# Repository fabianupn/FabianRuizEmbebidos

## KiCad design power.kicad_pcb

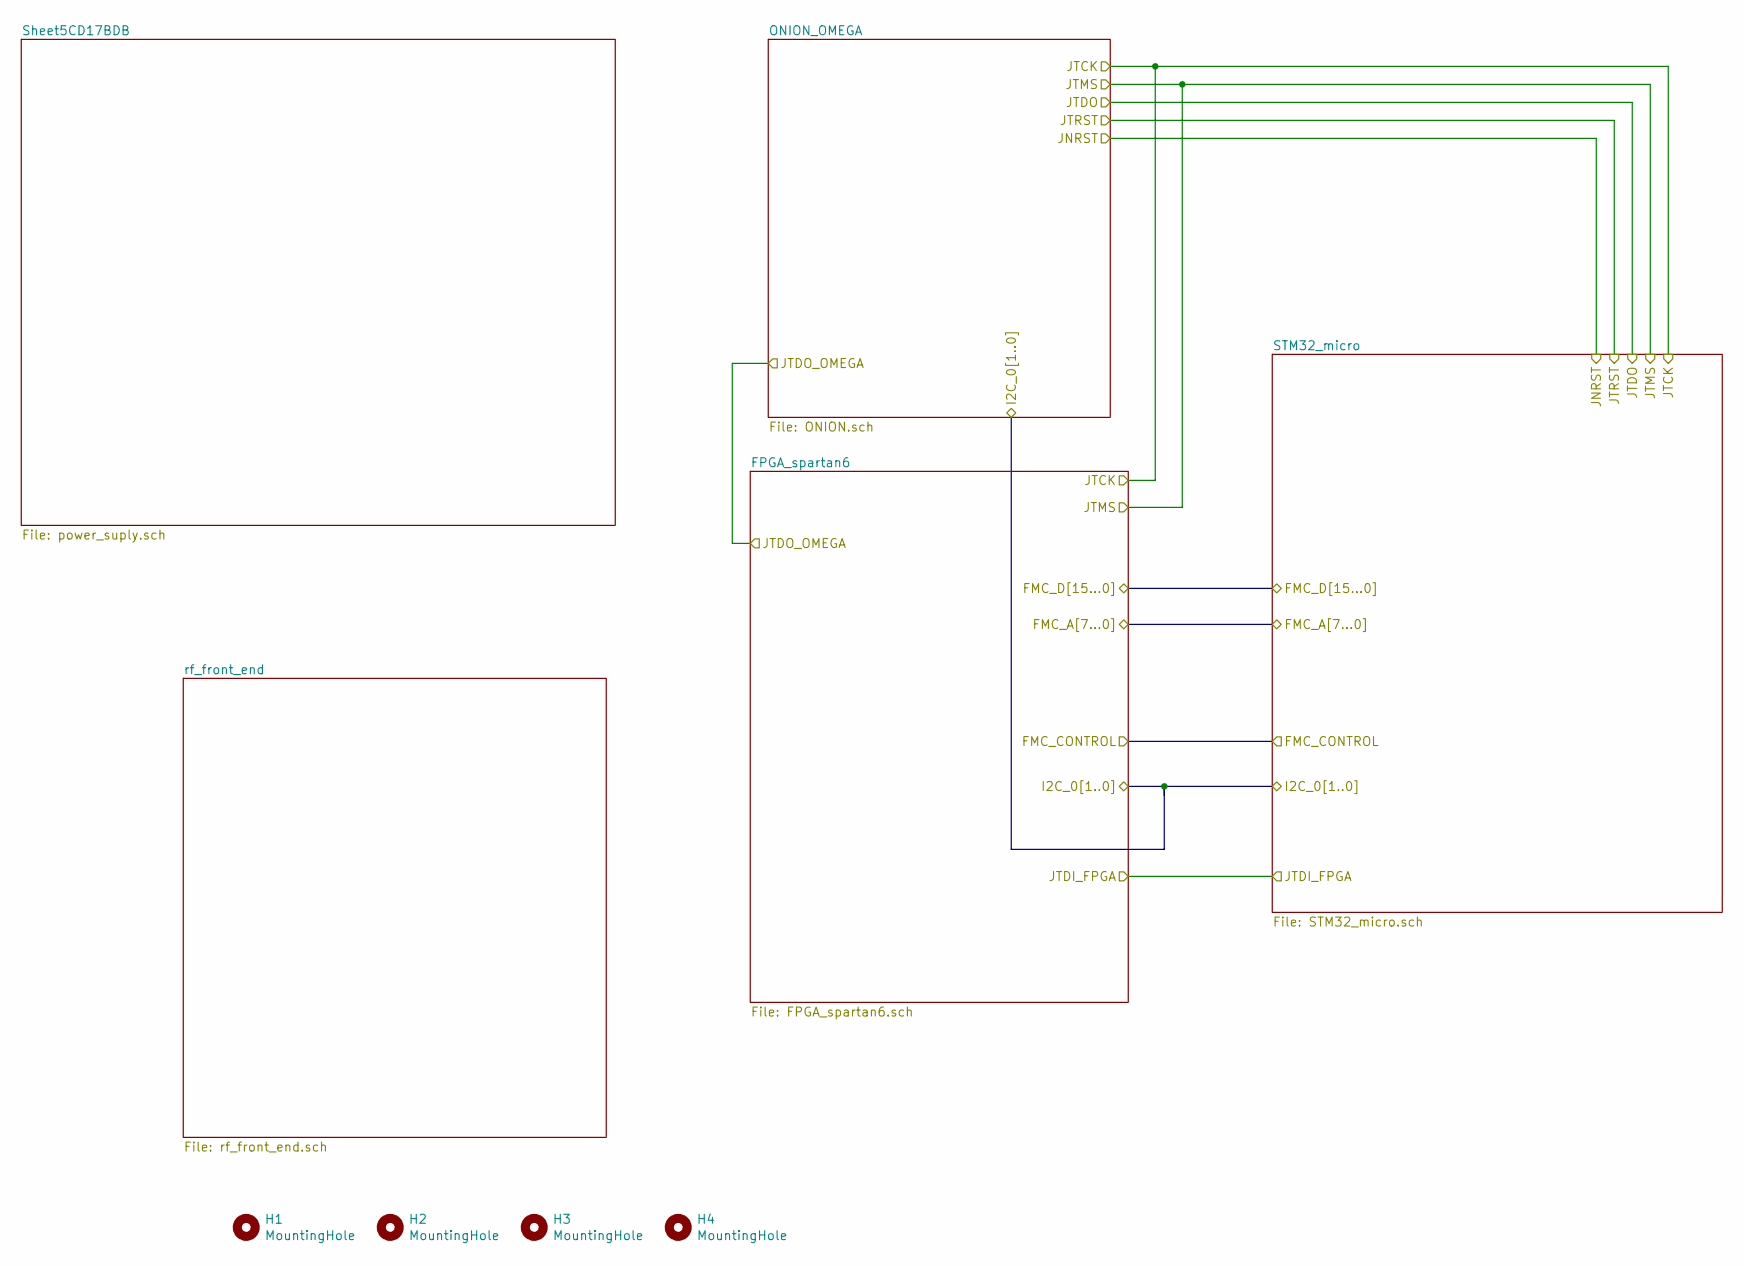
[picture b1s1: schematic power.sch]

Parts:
H1, H2, H3, H4: MountingHole; MountingHole_2.7mm_M2.5_ISO14580_Pad

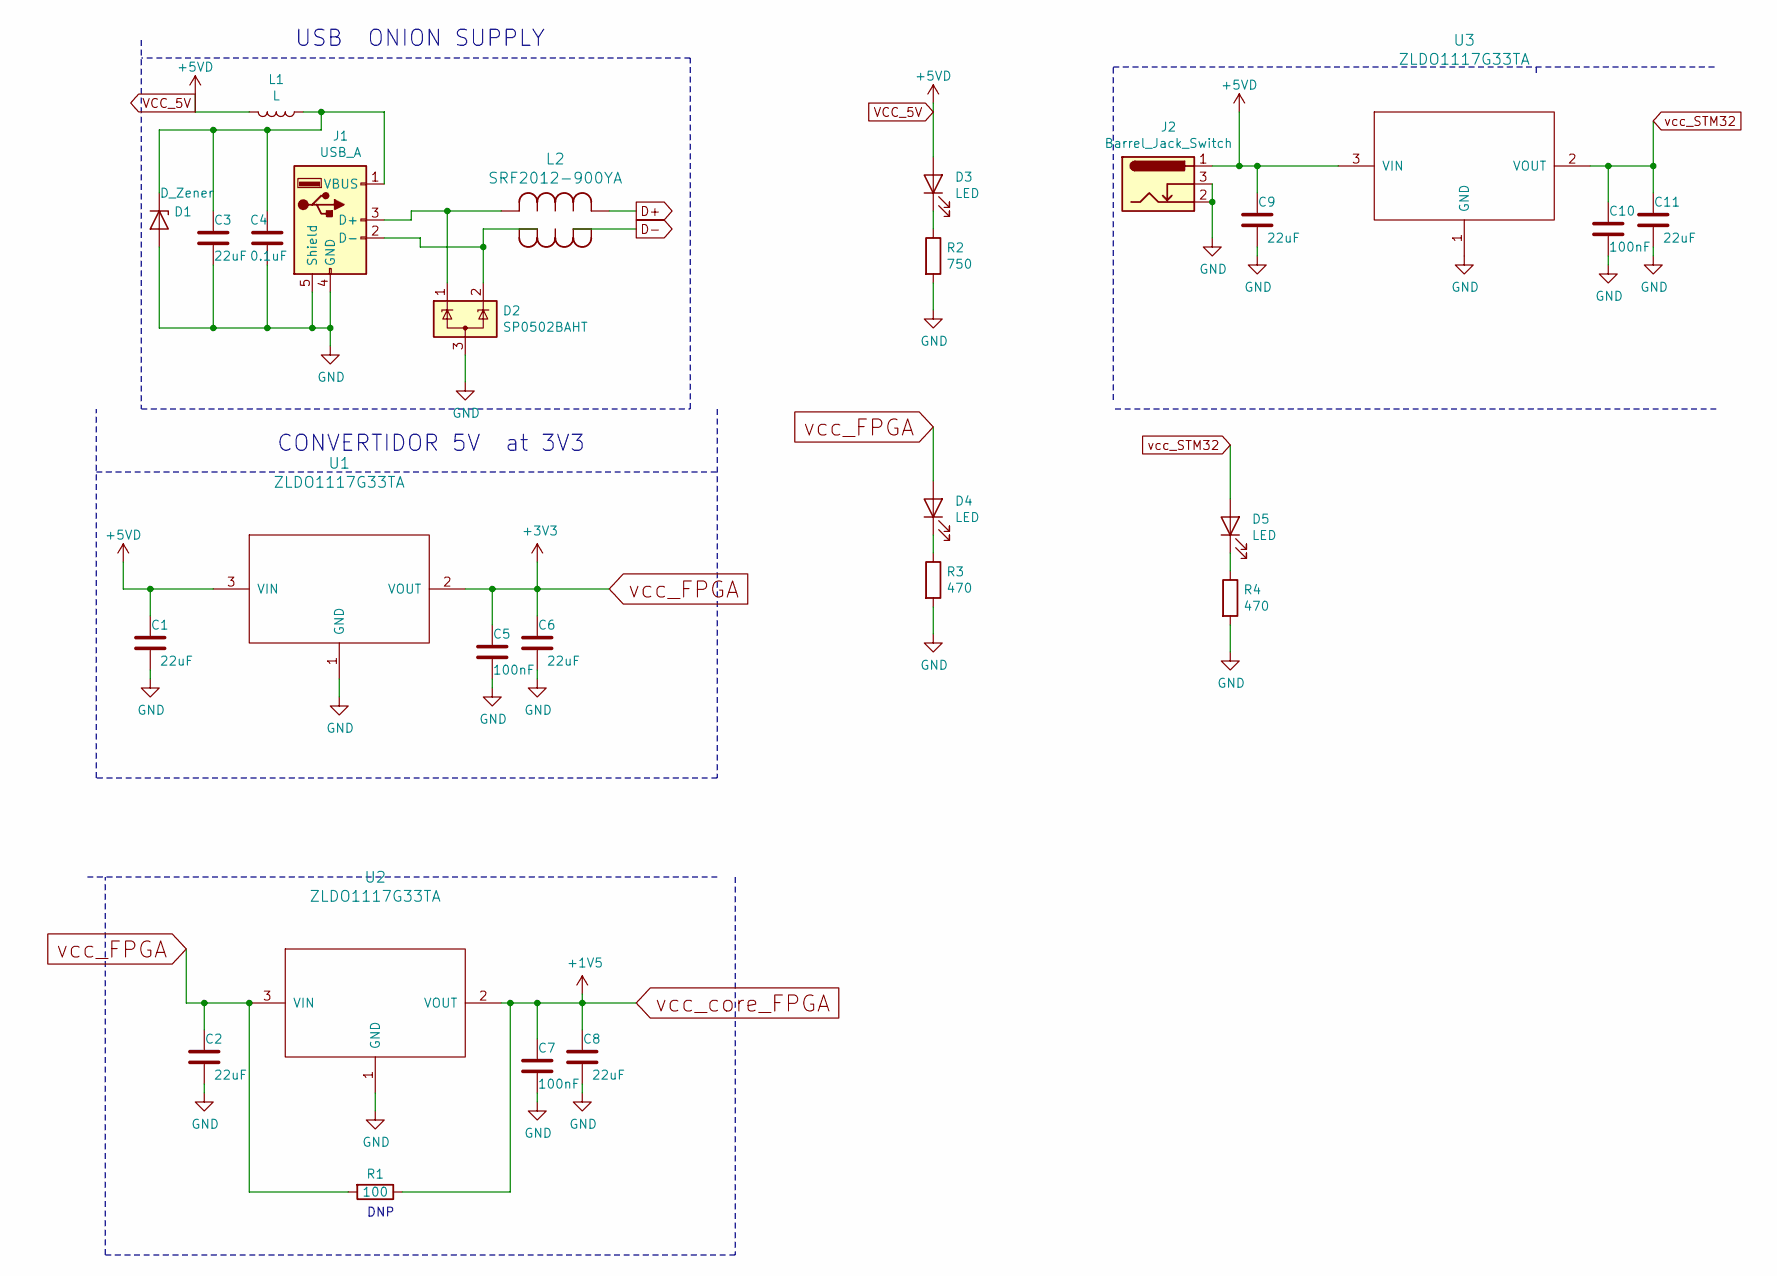
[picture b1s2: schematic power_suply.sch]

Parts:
C1, C2, C3, C6, C8, C9, C11: 22uF; C_0603_1608Metric_Pad1.05x0.95mm_HandSolder
C4: 0.1uF; C_0603_1608Metric_Pad1.05x0.95mm_HandSolder
C5, C7, C10: 100nF; C_0603_1608Metric_Pad1.05x0.95mm_HandSolder
D1: D_Zener; D_SOD-123; digikey MMSZ5231BT1GOSCT-ND
D2: SP0502BAHT; SOT-23
D3: LED; LED_0603_1608Metric_Pad1.05x0.95mm_HandSolder; digikey 160-1436-1-ND rojo
D4: LED; LED_0603_1608Metric_Pad1.05x0.95mm_HandSolder; digikey 846-1176-1-ND Verde
D5: LED; LED_0603_1608Metric_Pad1.05x0.95mm_HandSolder; digikey 160-1837-1-ND azul
J1: USB_A; USB_A_CNCTech_1001-011-01101_Horizontal
J2: Barrel_Jack_Switch; CUI_PJ-002A; digikey CP-002A-ND
L1: L; L_0603_1608Metric_Pad1.05x0.95mm_HandSolder; digikey 732-1593-1-ND
L2: SRF2012-900YA
R1: 100; R_0603_1608Metric_Pad1.05x0.95mm_HandSolder
R2: 750; R_0603_1608Metric_Pad1.05x0.95mm_HandSolder
R3, R4: 470; R_0603_1608Metric_Pad1.05x0.95mm_HandSolder
U1, U2, U3: ZLDO1117G33TA; SOT-223-3_TabPin2

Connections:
D+: L2.2; also elsewhere on the board
D-: L2.3; also elsewhere on the board
GND: C1.2, C2.2, C3.2, C4.2, C5.2, C6.2, C7.2, C8.2, C9.2, C10.2, C11.2, D1.2 (A), D2.3 (A), J1.4 (GND), J1.5 (Shield), J2.2, J2.3, R2.2, R3.2, R4.2, U1.1 (GND), U2.1 (GND), U3.1 (GND); also elsewhere on the board
unnamed: C3.1, C4.1, D1.1 (K), J1.1 (VBUS), L1.1
unnamed: D2.1 (K), J1.3 (D+), L2.1
unnamed: D2.2 (K), J1.2 (D-), L2.4
unnamed: D3.1 (K), R2.1
unnamed: D4.1 (K), R3.1
unnamed: D5.1 (K), R4.1
VCC_5V: C1.1, C9.1, D3.2 (A), J2.1, L1.2, U1.3 (VIN), U3.3 (VIN); also elsewhere on the board
vcc_FPGA: C2.1, C5.1, C6.1, D4.2 (A), R1.2, U1.2 (VOUT), U2.3 (VIN); also elsewhere on the board
vcc_STM32: C10.1, C11.1, D5.2 (A), U3.2 (VOUT); also elsewhere on the board
vcc_core_FPGA: C7.1, C8.1, R1.1, U2.2 (VOUT); also elsewhere on the board

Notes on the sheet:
USB ONION SUPPLY
CONVERTIDOR 5V at 3V3
DNP

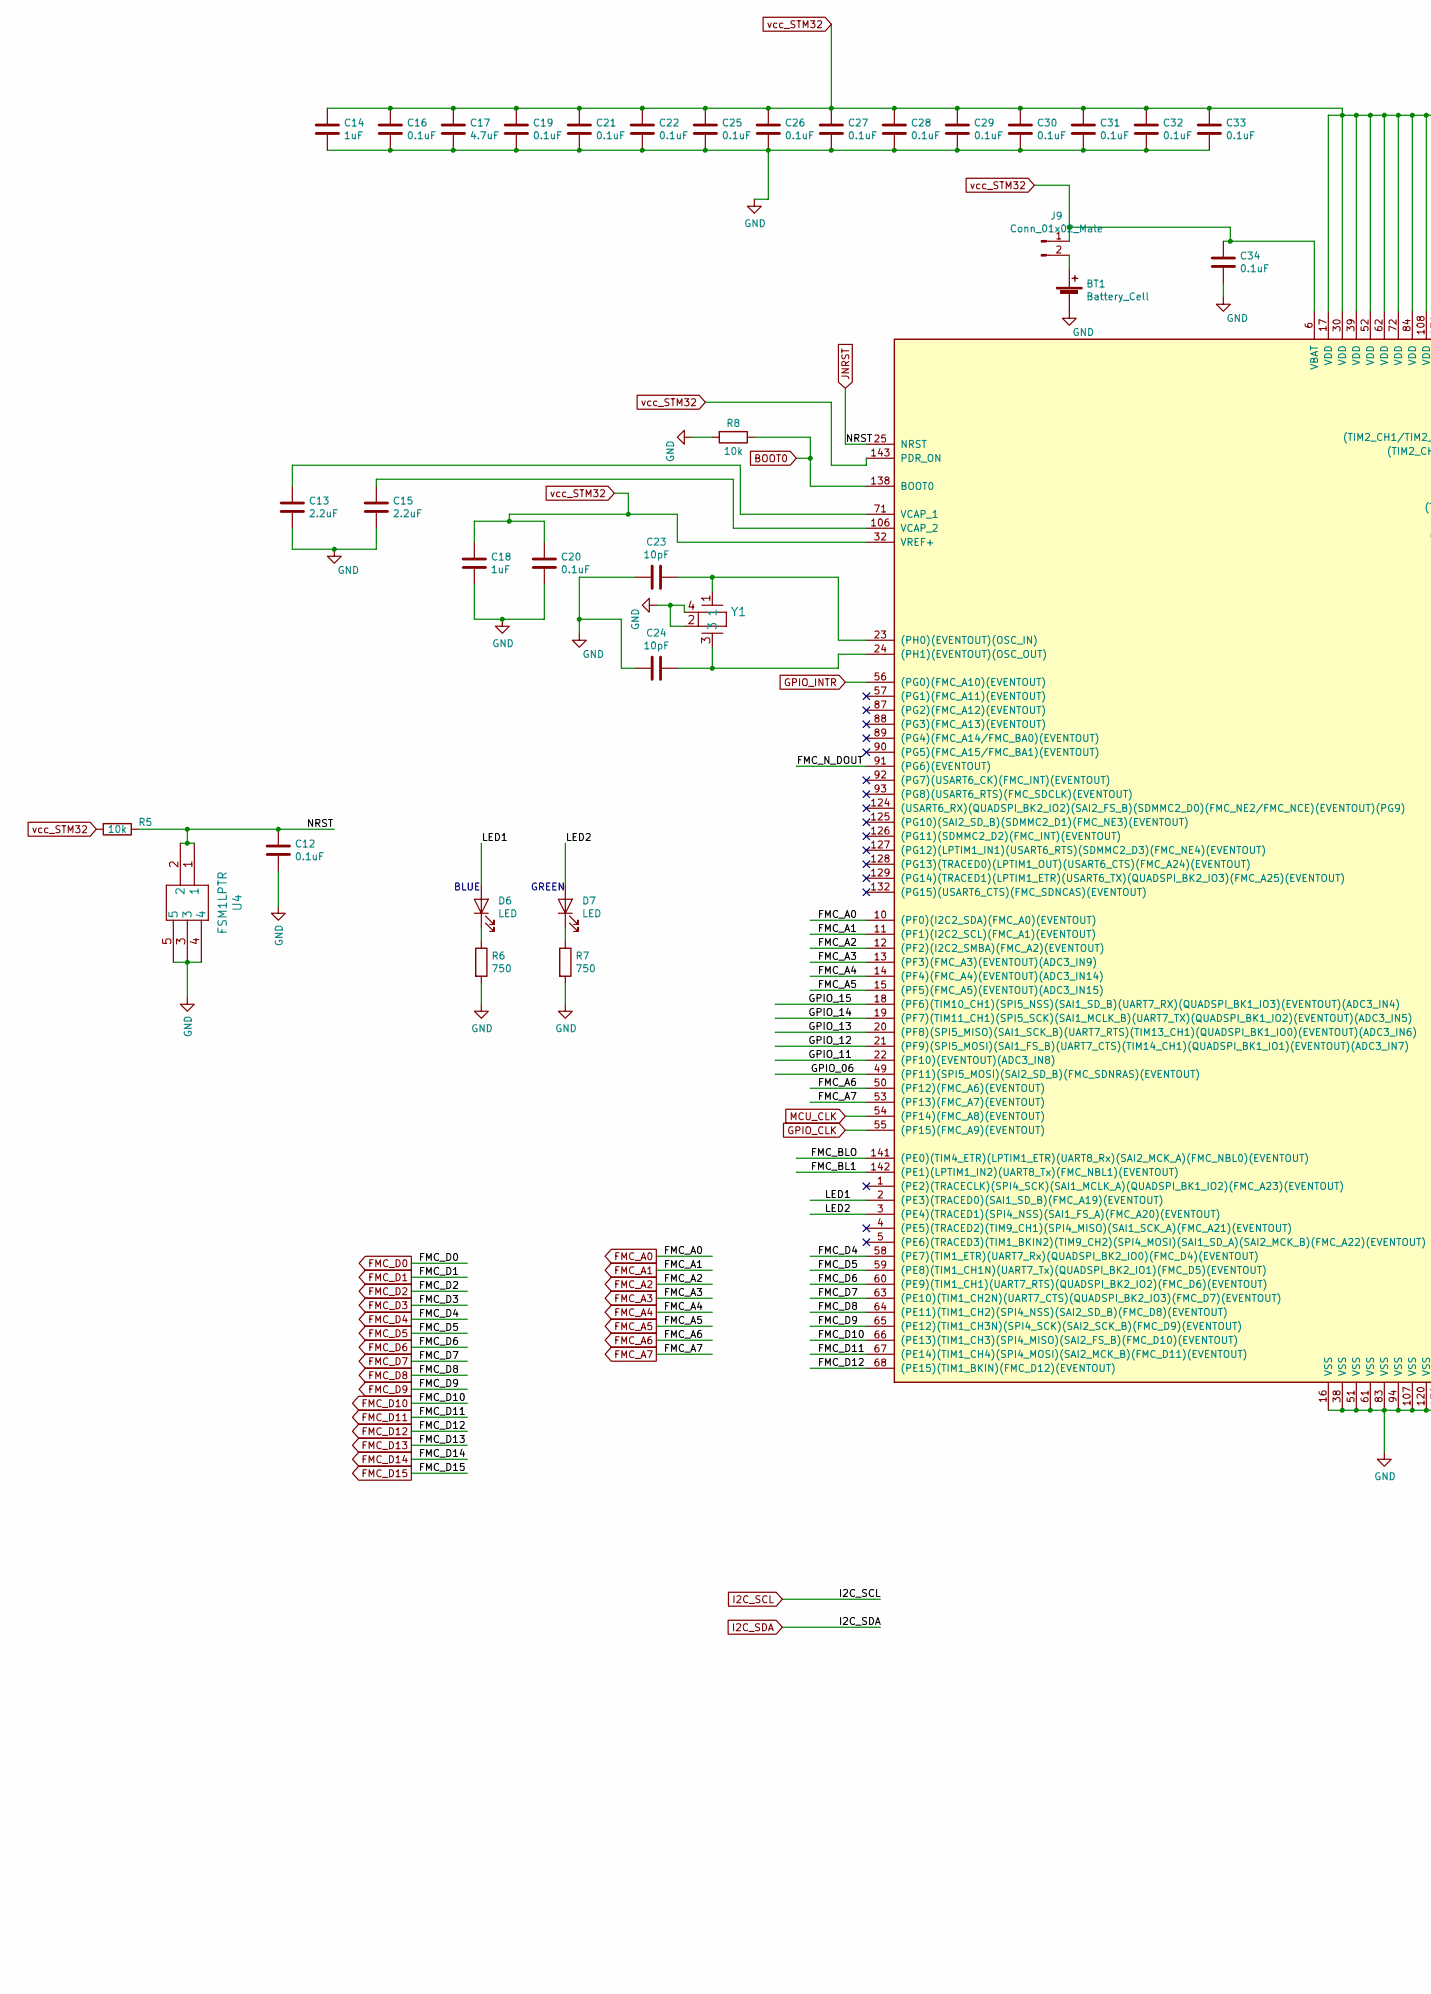
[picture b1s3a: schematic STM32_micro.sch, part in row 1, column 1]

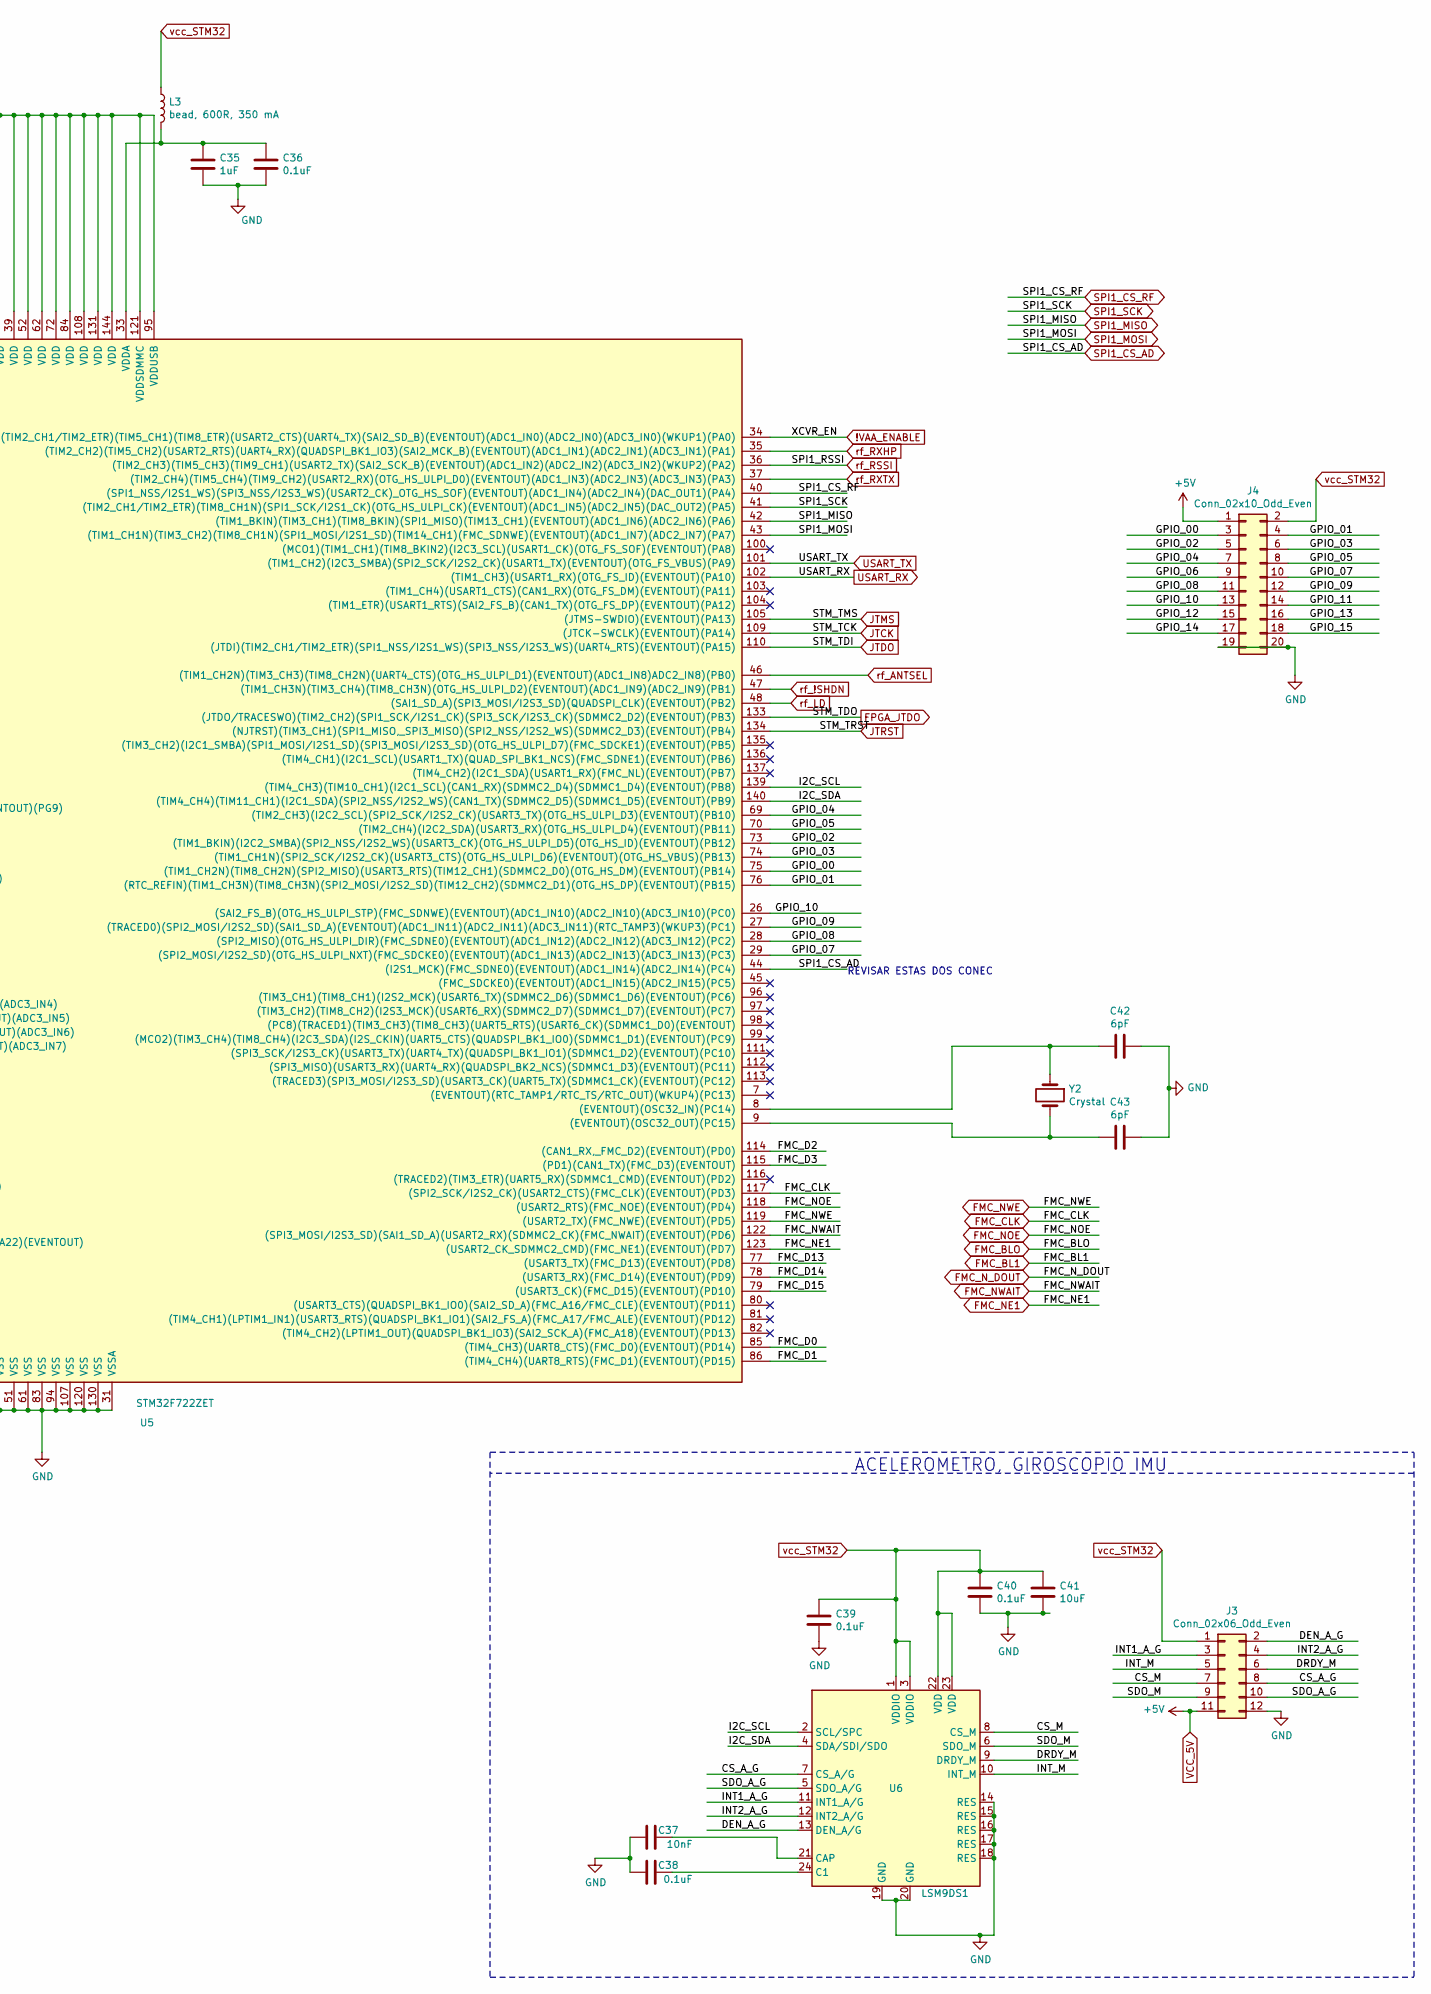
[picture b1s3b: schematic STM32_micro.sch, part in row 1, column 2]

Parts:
BT1: Battery_Cell; MPD_BK-870
C12, C16, C19, C20, C21, C22, C25, C26, C27, C28, C29, C30, C31, C32, C33, C34, C36, C38, C39, C40: 0.1uF; C_0603_1608Metric_Pad1.05x0.95mm_HandSolder
C13, C15: 2.2uF; C_0603_1608Metric_Pad1.05x0.95mm_HandSolder
C14, C18, C35: 1uF; C_0603_1608Metric_Pad1.05x0.95mm_HandSolder
C17: 4.7uF; C_0603_1608Metric_Pad1.05x0.95mm_HandSolder
C23, C24: 10pF; C_0603_1608Metric_Pad1.05x0.95mm_HandSolder
C37: 10nF; C_0603_1608Metric_Pad1.05x0.95mm_HandSolder
C41: 10uF; C_0603_1608Metric_Pad1.05x0.95mm_HandSolder
C42, C43: 6pF; C_0603_1608Metric_Pad1.05x0.95mm_HandSolder
D6: LED; LED_0603_1608Metric_Pad1.05x0.95mm_HandSolder; digikey 160-2032-1-ND BLUE
D7: LED; LED_0603_1608Metric_Pad1.05x0.95mm_HandSolder; digikey 846-1176-1-ND Verde
J3: Conn_02x06_Odd_Even; PinHeader_2x06_P2.54mm_Vertical
J4: Conn_02x10_Odd_Even; PinHeader_2x10_P2.54mm_Vertical; digikey S6106-ND
J9: Conn_01x02_Male; PinHeader_1x02_P2.54mm_Vertical
L3: bead, 600R, 350 mA; L_0603_1608Metric_Pad1.05x0.95mm_HandSolder
R5, R8: 10k; R_0603_1608Metric_Pad1.05x0.95mm_HandSolder
R6, R7: 750; R_0603_1608Metric_Pad1.05x0.95mm_HandSolder
U4: FSM1LPTR; digikey 450-1756-1-ND
U5: STM32F722ZET; LQFP-144_20x20mm_P0.5mm; digikey 497-18558-ND
U6: LSM9DS1; LGA-24L_3x3.5mm_P0.43mm; digikey 497-14946-1-ND
Y1: ABM8G-16.000MHZ-B4Y-T; GSG-XTAL3.2x2.5mm; digikey 535-10289-1-ND
Y2: Crystal; NX3215SA

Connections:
!VAA_ENABLE: U5.34 ((TIM2_CH1/TIM2_ETR)(TIM5_CH1)(TIM8_ETR)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); also elsewhere on the board
/STM32_micro/CS_A_G: J3.8, U6.7 (CS_A/G)
/STM32_micro/CS_M: J3.7, U6.8 (CS_M)
/STM32_micro/DEN_A_G: J3.2, U6.13 (DEN_A/G)
/STM32_micro/DRDY_M: J3.6, U6.9 (DRDY_M)
/STM32_micro/GPIO_00: J4.3, U5.75 ((TIM1_CH2N)(TIM8_CH2N)(SPI2_MISO)(USART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)
/STM32_micro/GPIO_01: J4.4, U5.76 ((RTC_REFIN)(TIM1_CH3N)(TIM8_CH3N)(SPI2_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)
/STM32_micro/GPIO_02: J4.5, U5.73 ((TIM1_BKIN)(I2C2_SMBA)(SPI2_NSS/I2S2_WS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)
/STM32_micro/GPIO_03: J4.6, U5.74 ((TIM1_CH1N)(SPI2_SCK/I2S2_CK)(USART3_CT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)
/STM32_micro/GPIO_04: J4.7, U5.69 ((TIM2_CH3)(I2C2_SCL)(SPI2_SCK/I2S2_CK)(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)
/STM32_micro/GPIO_05: J4.8, U5.70 ((TIM2_CH4)(I2C2_SDA)(USART3_RX)(OTG_HS_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)
/STM32_micro/GPIO_06: J4.9, U5.49 ((PF11)(SPI5_MOSI)(SAI2_SD_B)(FMC_SDNRAS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)
/STM32_micro/GPIO_07: J4.10, U5.29 ((SPI2_MOSI/I2S2_SD)(OTG_HS_ULPI_NXT)(FM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)
/STM32_micro/GPIO_08: J4.11, U5.28 ((SPI2_MISO)(OTG_HS_ULPI_DIR)(FMC_SDNE0)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)
/STM32_micro/GPIO_09: J4.12, U5.27 ((TRACED0)(SPI2_MOSI/I2S2_SD)(SAI1_SD_A)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)
/STM32_micro/GPIO_10: J4.13, U5.26 ((SAI2_FS_B)(OTG_HS_ULPI_STP)(FMC_SDNWE)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)
/STM32_micro/GPIO_11: J4.14, U5.22 ((PF10)(EVENTOUT)(ADC3_IN8))
/STM32_micro/GPIO_12: J4.15, U5.21 ((PF9)(SPI5_MOSI)(SAI1_FS_B)(UART7_CTS)(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)
/STM32_micro/GPIO_13: J4.16, U5.20 ((PF8)(SPI5_MISO)(SAI1_SCK_B)(UART7_RTS)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)
/STM32_micro/GPIO_14: J4.17, U5.19 ((PF7)(TIM11_CH1)(SPI5_SCK)(SAI1_MCLK_B)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)
/STM32_micro/GPIO_15: J4.18, U5.18 ((PF6)(TIM10_CH1)(SPI5_NSS)(SAI1_SD_B)(U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)
/STM32_micro/INT1_A_G: J3.3, U6.11 (INT1_A/G)
/STM32_micro/INT2_A_G: J3.4, U6.12 (INT2_A/G)
/STM32_micro/INT_M: J3.5, U6.10 (INT_M)
/STM32_micro/LED1: D6.2 (A), U5.2 ((PE3)(TRACED0)(SAI1_SD_B)(FMC_A19)(EVEN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)
/STM32_micro/LED2: D7.2 (A), U5.3 ((PE4)(TRACED1)(SPI4_NSS)(SAI1_FS_A)(FMC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)
/STM32_micro/SDO_A_G: J3.10, U6.5 (SDO_A/G)
/STM32_micro/SDO_M: J3.9, U6.6 (SDO_M)
BOOT0: R8.1, U5.138 (BOOT0); also elsewhere on the board
FMC_A0: U5.10 ((PF0)(I2C2_SDA)(FMC_A0)(EVENTOUT)); also elsewhere on the board
FMC_A1: U5.11 ((PF1)(I2C2_SCL)(FMC_A1)(EVENTOUT)); also elsewhere on the board
FMC_A2: U5.12 ((PF2)(I2C2_SMBA)(FMC_A2)(EVENTOUT)); also elsewhere on the board
FMC_A3: U5.13 ((PF3)(FMC_A3)(EVENTOUT)(ADC3_IN9)); also elsewhere on the board
FMC_A4: U5.14 ((PF4)(FMC_A4)(EVENTOUT)(ADC3_IN14)); also elsewhere on the board
FMC_A5: U5.15 ((PF5)(FMC_A5)(EVENTOUT)(ADC3_IN15)); also elsewhere on the board
FMC_A6: U5.50 ((PF12)(FMC_A6)(EVENTOUT)); also elsewhere on the board
FMC_A7: U5.53 ((PF13)(FMC_A7)(EVENTOUT)); also elsewhere on the board
FMC_BL1: U5.142 ((PE1)(LPTIM1_IN2)(UART8_Tx)(FMC_NBL1)(E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); also elsewhere on the board
FMC_BLO: U5.141 ((PE0)(TIM4_ETR)(LPTIM1_ETR)(UART8_Rx)(S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); also elsewhere on the board
FMC_CLK: U5.117 ((SPI2_SCK/I2S2_CK)(USART2_CTS)(FMC_CLK)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); also elsewhere on the board
FMC_D0: U5.85 ((TIM4_CH3)(UART8_CTS)(FMC_D0)(EVENTOUT)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); also elsewhere on the board
FMC_D1: U5.86 ((TIM4_CH4)(UART8_RTS)(FMC_D1)(EVENTOUT)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); also elsewhere on the board
FMC_D2: U5.114 ((CAN1_RX,_FMC_D2)(EVENTOUT)(PD0)); also elsewhere on the board
FMC_D3: U5.115 ((PD1)(CAN1_TX)(FMC_D3)(EVENTOUT)); also elsewhere on the board
FMC_D4: U5.58 ((PE7)(TIM1_ETR)(UART7_Rx)(QUADSPI_BK2_I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); also elsewhere on the board
FMC_D5: U5.59 ((PE8)(TIM1_CH1N)(UART7_Tx)(QUADSPI_BK2_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); also elsewhere on the board
FMC_D6: U5.60 ((PE9)(TIM1_CH1)(UART7_RTS)(QUADSPI_BK2_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); also elsewhere on the board
FMC_D7: U5.63 ((PE10)(TIM1_CH2N)(UART7_CTS)(QUADSPI_BK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); also elsewhere on the board
FMC_D8: U5.64 ((PE11)(TIM1_CH2)(SPI4_NSS)(SAI2_SD_B)(F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); also elsewhere on the board
FMC_D9: U5.65 ((PE12)(TIM1_CH3N)(SPI4_SCK)(SAI2_SCK_B)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); also elsewhere on the board
FMC_D10: U5.66 ((PE13)(TIM1_CH3)(SPI4_MISO)(SAI2_FS_B)(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); also elsewhere on the board
FMC_D11: U5.67 ((PE14)(TIM1_CH4)(SPI4_MOSI)(SAI2_MCK_B)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); also elsewhere on the board
FMC_D12: U5.68 ((PE15)(TIM1_BKIN)(FMC_D12)(EVENTOUT)); also elsewhere on the board
FMC_D13: U5.77 ((USART3_TX)(FMC_D13)(EVENTOUT)(PD8)); also elsewhere on the board
FMC_D14: U5.78 ((USART3_RX)(FMC_D14)(EVENTOUT)(PD9)); also elsewhere on the board
FMC_D15: U5.79 ((USART3_CK)(FMC_D15)(EVENTOUT)(PD10)); also elsewhere on the board
FMC_NE1: U5.123 ((USART2_CK_SDMMC2_CMD)(FMC_NE1)(EVENTOU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); also elsewhere on the board
FMC_NOE: U5.118 ((USART2_RTS)(FMC_NOE)(EVENTOUT)(PD4)); also elsewhere on the board
FMC_NWAIT: U5.122 ((SPI3_MOSI/I2S3_SD)(SAI1_SD_A)(USART2_R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); also elsewhere on the board
FMC_NWE: U5.119 ((USART2_TX)(FMC_NWE)(EVENTOUT)(PD5)); also elsewhere on the board
FMC_N_DOUT: U5.91 ((PG6)(EVENTOUT)); also elsewhere on the board
FPGA_JTDO: U5.133 ((JTDO/TRACESWO)(TIM2_CH2)(SPI1_SCK/I2S1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); also elsewhere on the board
GND: BT1.2 (-), C12.2, C13.2, C14.2, C15.2, C16.2, C17.2, C18.2, C19.2, C20.2, C21.2, C22.2, C23.2, C24.1, C25.2, C26.2, C27.2, C28.2, C29.2, C30.2, C31.2, C32.2, C33.2, C34.2, C35.2, C36.2, C37.1, C38.1, C39.2, C40.2, C41.2, C42.1, C43.1, J3.12, J4.19, J4.20, R6.2, R7.2, R8.2, U4.3, U4.4, U4.5, U5.16 (VSS), U5.31 (VSSA), U5.38 (VSS), U5.51 (VSS), U5.61 (VSS), U5.83 (VSS), U5.94 (VSS), U5.107 (VSS), U5.120 (VSS), U5.130 (VSS), U6.14 (RES), U6.15 (RES), U6.16 (RES), U6.17 (RES), U6.18 (RES), U6.19 (GND), U6.20 (GND), Y1.2, Y1.4; also elsewhere on the board
GPIO_CLK: U5.55 ((PF15)(FMC_A9)(EVENTOUT)); also elsewhere on the board
GPIO_INTR: U5.56 ((PG0)(FMC_A10)(EVENTOUT)); also elsewhere on the board
I2C_SCL: U5.139 ((TIM4_CH3)(TIM10_CH1)(I2C1_SCL)(CAN1_RX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), U6.2 (SCL/SPC); also elsewhere on the board
I2C_SDA: U5.140 ((TIM4_CH4)(TIM11_CH1)(I2C1_SDA)(SPI2_NS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), U6.4 (SDA/SDI/SDO); also elsewhere on the board
JNRST: C12.1, R5.1, U4.1, U4.2, U5.25 (NRST); also elsewhere on the board
JTCK: U5.109 ((JTCK-SWCLK)(EVENTOUT)(PA14)); also elsewhere on the board
JTDO: U5.110 ((JTDI)(TIM2_CH1/TIM2_ETR)(SPI1_NSS/I2S1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); also elsewhere on the board
JTMS: U5.105 ((JTMS-SWDIO)(EVENTOUT)(PA13)); also elsewhere on the board
JTRST: U5.134 ((NJTRST)(TIM3_CH1)(SPI1_MISO,_SPI3_MISO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); also elsewhere on the board
MCU_CLK: U5.54 ((PF14)(FMC_A8)(EVENTOUT)); also elsewhere on the board
unnamed: BT1.1 (+), J9.2
unnamed: C13.1, U5.71 (VCAP_1)
unnamed: C15.1, U5.106 (VCAP_2)
unnamed: C23.1, U5.23 ((PH0)(EVENTOUT)(OSC_IN)), Y1.1
unnamed: C24.2, U5.24 ((PH1)(EVENTOUT)(OSC_OUT)), Y1.3
unnamed: C35.1, C36.1, L3.2, U5.33 (VDDA)
unnamed: C37.2, U6.21 (CAP)
unnamed: C38.2, U6.24 (C1)
unnamed: C42.2, U5.8 ((EVENTOUT)(OSC32_IN)(PC14)), Y2.1
unnamed: C43.2, U5.9 ((EVENTOUT)(OSC32_OUT)(PC15)), Y2.2
unnamed: D6.1 (K), R6.1
unnamed: D7.1 (K), R7.1
SPI1_CS_AD: U5.44 ((I2S1_MCK)(FMC_SDNE0)(EVENTOUT)(ADC1_IN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); also elsewhere on the board
SPI1_CS_RF: U5.40 ((SPI1_NSS/I2S1_WS)(SPI3_NSS/I2S3_WS)(US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); also elsewhere on the board
SPI1_MISO: U5.42 ((TIM1_BKIN)(TIM3_CH1)(TIM8_BKIN)(SPI1_M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); also elsewhere on the board
SPI1_MOSI: U5.43 ((TIM1_CH1N)(TIM3_CH2)(TIM8_CH1N)(SPI1_M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); also elsewhere on the board
SPI1_RSSI: U5.36 ((TIM2_CH3)(TIM5_CH3)(TIM9_CH1)(USART2_T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); also elsewhere on the board
SPI1_SCK: U5.41 ((TIM2_CH1/TIM2_ETR)(TIM8_CH1N)(SPI1_SCK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); also elsewhere on the board
USART_RX: U5.102 ((TIM1_CH3)(USART1_RX)(OTG_FS_ID)(EVENTO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); also elsewhere on the board
USART_TX: U5.101 ((TIM1_CH2)(I2C3_SMBA)(SPI2_SCK/I2S2_CK)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); also elsewhere on the board
VCC_5V: J3.11, J4.1; also elsewhere on the board
rf_!SHDN: U5.47 ((TIM1_CH3N)(TIM3_CH4)(TIM8_CH3N)(OTG_HS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); also elsewhere on the board
rf_ANTSEL: U5.46 ((TIM1_CH2N)(TIM3_CH3)(TIM8_CH2N)(UART4_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); also elsewhere on the board
rf_LD: U5.48 ((SAI1_SD_A)(SPI3_MOSI/I2S3_SD)(QUADSPI_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); also elsewhere on the board
rf_RXHP: U5.35 ((TIM2_CH2)(TIM5_CH2)(USART2_RTS)(UART4_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); also elsewhere on the board
rf_RXTX: U5.37 ((TIM2_CH4)(TIM5_CH4)(TIM9_CH2)(USART2_R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); also elsewhere on the board
vcc_STM32: C14.1, C16.1, C17.1, C18.1, C19.1, C20.1, C21.1, C22.1, C25.1, C26.1, C27.1, C28.1, C29.1, C30.1, C31.1, C32.1, C33.1, C34.1, C39.1, C40.1, C41.1, J3.1, J4.2, J9.1, L3.1, R5.2, U5.6 (VBAT), U5.17 (VDD), U5.30 (VDD), U5.32 (VREF+), U5.39 (VDD), U5.52 (VDD), U5.62 (VDD), U5.72 (VDD), U5.84 (VDD), U5.95 (VDDUSB), U5.108 (VDD), U5.121 (VDDSDMMC), U5.131 (VDD), U5.143 (PDR_ON), U5.144 (VDD), U6.1 (VDDIO), U6.3 (VDDIO), U6.22 (VDD), U6.23 (VDD); also elsewhere on the board

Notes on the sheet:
ACELEROMETRO, GIROSCOPIO IMU
REVISAR ESTAS DOS CONEC
BLUE
GREEN

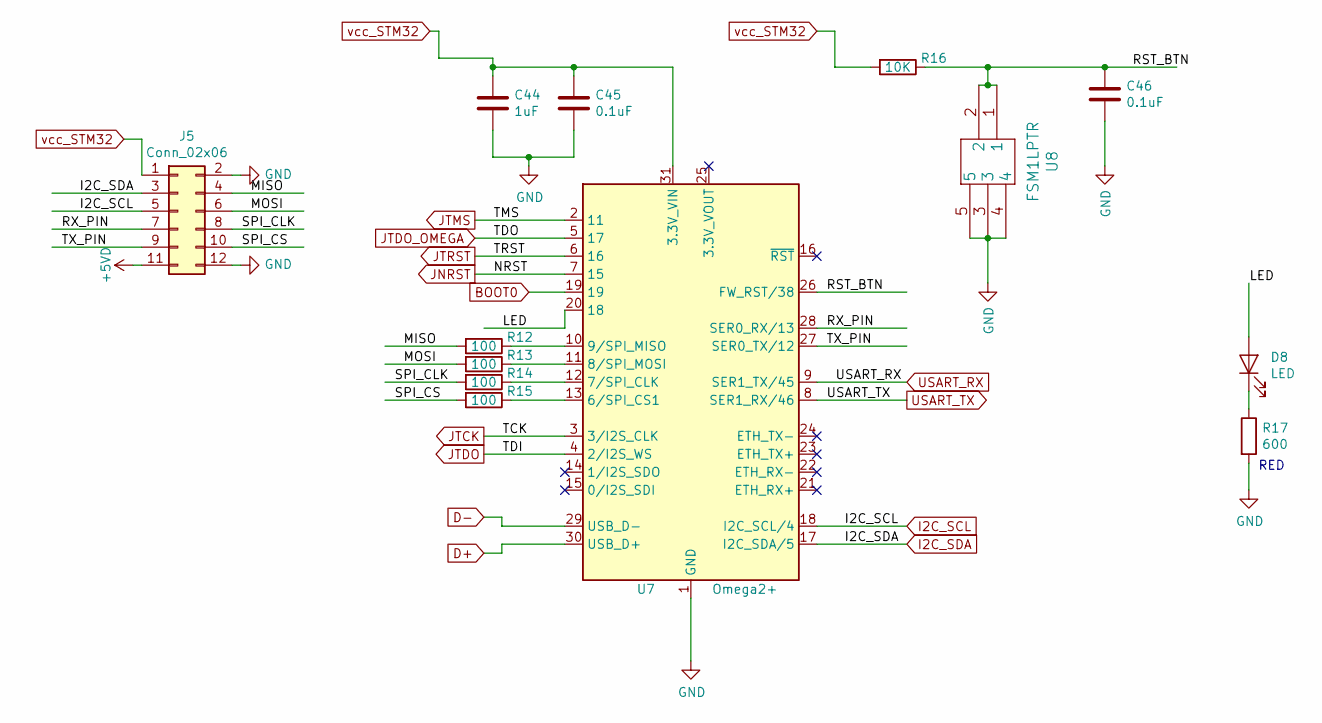
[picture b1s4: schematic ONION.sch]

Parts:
C44: 1uF; C_0603_1608Metric_Pad1.05x0.95mm_HandSolder
C45, C46: 0.1uF; C_0603_1608Metric_Pad1.05x0.95mm_HandSolder
D8: LED; LED_0603_1608Metric_Pad1.05x0.95mm_HandSolder; digikey 160-1436-1-ND rojo
J5: Conn_02x06; PinHeader_2x06_P2.54mm_Vertical
R12, R13, R14, R15: 100; R_0603_1608Metric_Pad1.05x0.95mm_HandSolder
R16: 10K; R_0603_1608Metric_Pad1.05x0.95mm_HandSolder
R17: 600; R_0603_1608Metric_Pad1.05x0.95mm_HandSolder
U7: Omega2+; Onion_Omega2+
U8: FSM1LPTR; digikey 450-1756-1-ND

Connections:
/ONION_OMEGA/LED: D8.2 (A), U7.20 (18)
/ONION_OMEGA/MISO: J5.4, R12.2
/ONION_OMEGA/MOSI: J5.6, R13.2
/ONION_OMEGA/RST_BTN: C46.1, R16.1, U7.26 (FW_RST/38), U8.1, U8.2
/ONION_OMEGA/RX_PIN: J5.7, U7.28 (SER0_RX/13)
/ONION_OMEGA/SPI_CLK: J5.8, R14.2
/ONION_OMEGA/SPI_CS: J5.10, R15.2
/ONION_OMEGA/TX_PIN: J5.9, U7.27 (SER0_TX/12)
BOOT0: U7.19; also elsewhere on the board
D+: U7.30 (USB_D+); also elsewhere on the board
D-: U7.29 (USB_D-); also elsewhere on the board
GND: C44.2, C45.2, C46.2, J5.2, J5.12, R17.2, U7.1 (GND), U7.32 (GND), U8.3, U8.4, U8.5; also elsewhere on the board
I2C_SCL: J5.5, U7.18 (I2C_SCL/4); also elsewhere on the board
I2C_SDA: J5.3, U7.17 (I2C_SDA/5); also elsewhere on the board
JNRST: U7.7 (15); also elsewhere on the board
JTCK: U7.3 (3/I2S_CLK); also elsewhere on the board
JTDO: U7.4 (2/I2S_WS); also elsewhere on the board
JTDO_OMEGA: U7.5 (17); also elsewhere on the board
JTMS: U7.2 (11); also elsewhere on the board
JTRST: U7.6 (16); also elsewhere on the board
unnamed: D8.1 (K), R17.1
unnamed: R12.1, U7.10 (9/SPI_MISO)
unnamed: R13.1, U7.11 (8/SPI_MOSI)
unnamed: R14.1, U7.12 (7/SPI_CLK)
unnamed: R15.1, U7.13 (6/SPI_CS1)
USART_RX: U7.9 (SER1_TX/45); also elsewhere on the board
USART_TX: U7.8 (SER1_RX/46); also elsewhere on the board
VCC_5V: J5.11; also elsewhere on the board
vcc_STM32: C44.1, C45.1, J5.1, R16.2, U7.31 (3.3V_VIN); also elsewhere on the board

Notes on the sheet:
RED

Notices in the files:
parts and their libraries:
Copyright 2016 Accelerated Designs. All rights reserved.
